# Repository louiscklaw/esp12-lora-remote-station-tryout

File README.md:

# esp12-lora-remote-station-tryout

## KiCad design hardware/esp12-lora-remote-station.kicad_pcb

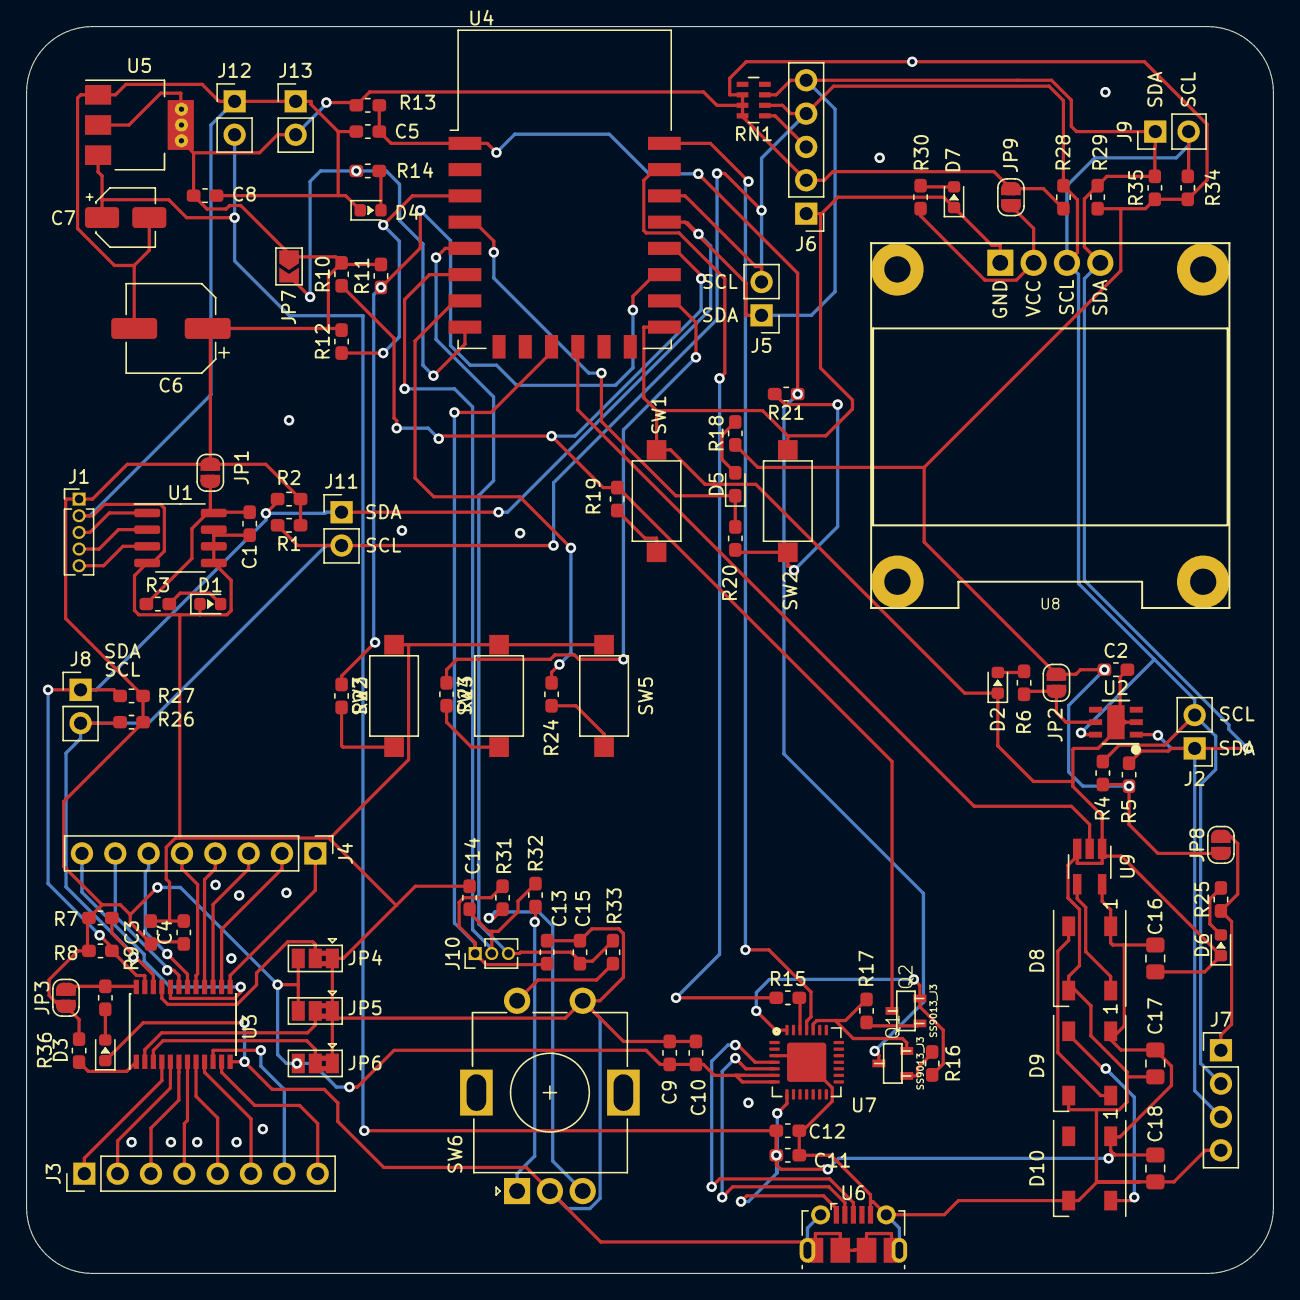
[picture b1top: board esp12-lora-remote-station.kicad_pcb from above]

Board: 2 copper layers, 95.0 x 95.0 mm, 104 parts (0 on the bottom side), 73 nets.

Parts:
C1: C103,0603; C_0603_1608Metric_Pad1.05x0.95mm_HandSolder
C2, C3, C8, C9, C11: C106,0603; C_0603_1608Metric_Pad1.05x0.95mm_HandSolder
C4, C5, C10, C12, C13, C14, C15: C104,0603; C_0603_1608Metric_Pad1.05x0.95mm_HandSolder
C6: CP100uf,10V; CP_Elec_6.3x5.3
C7: CP10uf,16V; CP_Elec_4x5.3
C16, C17, C18: C106,0805; C_0805_2012Metric_Pad1.15x1.40mm_HandSolder
D1, D2, D3, D4, D6, D7: LED_GREEN,0603; LED_0603_1608Metric
D5: LED_BLUE,0603; LED_0603_1608Metric_Pad1.05x0.95mm_HandSolder
D8, D9, D10: WS2812B; LED_WS2812B_5050_white
J1: LM75_HEADER; PinHeader_1x05_P1.27mm_Vertical
J2, J5, J8, J9, J11: I2C_HEADER,2.54; I2C_DEBUG,2.54
J3: P0_HEADER; PinHeader_1x08_P2.54mm_Vertical
J4: P1_HEADER; PinHeader_1x08_P2.54mm_Vertical
J6: I2C_HEADER; PinHeader_1x05_P2.54mm_Vertical
J7: GSM_TX_HEADER; PinHeader_1x04_P2.54mm_Vertical
J10: ROT_ENC_HEADER; PinHeader_1x03_P1.27mm_Vertical
J12, J13: 5V_header; PinHeader_1x02_P2.54mm_Vertical
JP1: LM75_EN; SolderJumper-2_P1.3mm_Open_RoundedPad1.0x1.5mm
JP2: SHT20_EN; SolderJumper-2_P1.3mm_Open_RoundedPad1.0x1.5mm
JP3: PCF8575C_EN; SolderJumper-2_P1.3mm_Open_RoundedPad1.0x1.5mm
JP4: A0; SolderJumper-3_P1.3mm_Bridged2Bar12_Pad1.0x1.5mm
JP5: A1; SolderJumper-3_P1.3mm_Bridged2Bar12_Pad1.0x1.5mm
JP6: A2; SolderJumper-3_P1.3mm_Bridged2Bar12_Pad1.0x1.5mm
JP7: SolderJumper_2_Open_arrow; SolderJumper-2_P1.3mm_Open_TrianglePad1.0x1.5mm
JP8: PWR_EN; SolderJumper-2_P1.3mm_Open_RoundedPad1.0x1.5mm
JP9: SolderJumper_2_Open_round; SolderJumper-2_P1.3mm_Open_RoundedPad1.0x1.5mm
Q1, Q2: SS9013_J3; 9013,J3,SOT23
R1, R2, R4, R5, R7, R8, R26, R27, R28, R29, R34, R35: R473,0603; R_0603_1608Metric_Pad1.05x0.95mm_HandSolder
R3, R6, R9, R14, R25, R30: R511,0603; R_0603_1608Metric_Pad1.05x0.95mm_HandSolder
R10, R11, R12, R13, R16, R17: R123,0603; R_0603_1608Metric_Pad1.05x0.95mm_HandSolder
R15, R18, R19, R21, R22, R23, R24: R471,0603; R_0603_1608Metric_Pad1.05x0.95mm_HandSolder
R20: R0,0603; R_0603_1608Metric_Pad1.05x0.95mm_HandSolder
R31, R32, R33: R273,0603; R_0603_1608Metric_Pad1.05x0.95mm_HandSolder
R36: R104,0603; R_0603_1608Metric_Pad1.05x0.95mm_HandSolder
RN1: RN_472,0603; R_Array_Concave_4x0603
SW1: FLASH_BUTTON; SW_SPST_CK_RS282G05A3
SW2: SW_RESET,2_leg,SMD; SW_SPST_CK_RS282G05A3
SW3, SW5: USER_BUTTON1; SW_SPST_CK_RS282G05A3
SW4: USER_BUTTON2; SW_SPST_CK_RS282G05A3
SW6: EC11_VERTICAL; RotaryEncoder_Alps_EC11E_Vertical_H20mm
U1: LM75; SOP-8_3.76x4.96mm_P1.27mm
U2: SHT20
U3: PCF8575C
U4: ESP12; ESP-12E
U5: AMS1117-3.3; AMS1117_SOT-223
U6: USB_Micro; USB_Micro-B_Molex-105017-0001
U7: CP2102; CP2102_qfn28
U8: SSD1306-OLED-I2C; OLED_096_12864_SSD1306
U9: 74AHCT1G125; SOT-23-5_HandSoldering

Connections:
+3V3: C2.1, C3.1, C4.1, C6.1, C8.1, C9.1, C10.1, J1.1, J6.2, J13.2, JP1.1, JP2.1, JP3.1, JP4.3, JP5.3, JP6.3, JP7.1, JP8.1, JP9.1, R1.1, R2.1, R4.1, R5.1, R7.1, R8.1, R10.2, R11.2, R12.2, R13.2, R18.1, R26.1, R27.1, R28.1, R29.1, R34.1, R35.1, R36.1, RN1.6, RN1.7, RN1.8, U5.2, U7.6, U7.7
+5V: C7.1, C11.1, C12.1, C16.2, C17.2, C18.2, D8.1, D9.1, D10.1, J12.2, U5.3, U6.1, U7.8, U9.5
/SCL: J2.SCL, J5.SCL, J6.4, J7.2, J8.SCL, J9.SCL, J11.SCL, R1.2, R4.2, R7.2, R26.2, R28.2, R34.2, RN1.2, U2.6, U3.22, U4.20, U8.SCL
/SDA: J2.SDA, J5.SDA, J6.5, J7.3, J8.SDA, J9.SDA, J11.SDA, R2.2, R5.2, R8.2, R27.2, R29.2, R35.2, RN1.3, U2.1, U3.23, U4.19, U8.SDA
/WS2812/WS2812_IN: U4.12, U9.2
/digital_input/A0: JP4.2, U3.21
/digital_input/A1: JP5.2, U3.2
/digital_input/A2: JP6.2, U3.3
/digital_input/INT: R36.2, U3.1
/digital_input/P10: J4.1, U3.13
/digital_input/P11: J4.2, U3.14
/digital_input/P12: J4.3, U3.15
/digital_input/P13: J4.4, U3.16
/digital_input/P14: J4.5, U3.17
/digital_input/P15: J4.6, U3.18
/digital_input/P16: J4.7, U3.19
/digital_input/P17: J4.8, U3.20
/digital_input/PO0: J3.1, U3.4
/digital_input/PO1: J3.2, U3.5
/digital_input/PO2: J3.3, U3.6
/digital_input/PO3: J3.4, U3.7
/digital_input/PO4: J3.5, U3.8
/digital_input/PO5: J3.6, U3.9
/digital_input/PO6: J3.7, U3.10
/digital_input/PO7: J3.8, U3.11
/esp12_core/EN: R12.1, U4.3
/esp12_core/GPIO0: Q2.3, R10.1, R19.1, U4.18
/esp12_core/GPIO2: R11.1, R22.1, U4.17
/esp12_core/GPIO13: R24.1, U4.7
/esp12_core/GPIO14: C15.1, J10.3, R33.2, U4.5
/esp12_core/GPIO15: R23.1, U4.16
/esp12_core/GPIO16: D5.1, R20.1, U4.4
/esp12_core/INT: J6.3, RN1.1
/esp12_core/RXD0: R15.1, U4.21
/esp12_core/TXD0: U4.22, U7.25
/esp12_core/nRST: C5.1, Q1.3, R13.1, R21.1, U4.1
/esp12_core/usb_to_uart/DTR: Q2.2, R16.1, U7.28
/esp12_core/usb_to_uart/D_N: U6.2, U7.5
/esp12_core/usb_to_uart/D_P: U6.3, U7.4
/esp12_core/usb_to_uart/RTS: Q1.2, R17.1, U7.24
/user_button/A: C13.1, J10.1, R31.2, U4.11
/user_button/B: C14.1, J10.2, R32.2, U4.6
GND: C1.2, C2.2, C3.2, C4.2, C5.2, C6.2, C7.2, C8.2, C9.2, C10.2, C11.2, C12.2, C13.2, C14.2, C15.2, C16.1, C17.1, C18.1, D1.1, D2.1, D3.1, D4.1, D6.1, D7.1, D8.3, D9.3, D10.3, J1.2, J6.1, J7.4, J12.1, J13.1, JP4.1, JP5.1, JP6.1, SW1.2, SW2.2, SW3.2, SW4.2, SW5.2, SW6.C, SW6.E, U1.4, U1.5, U1.6, U1.7, U2.2, U2.PAD, U3.12, U4.15, U5.1, U6.5, U6.6, U6.7, U6.8, U6.9, U7.3, U7.29, U8.GND, U9.1, U9.3
unnamed: C1.1, JP1.2, R3.1, U1.8
unnamed: D1.2, R3.2
unnamed: D2.2, R6.2
unnamed: D3.2, R9.2
unnamed: D4.2, R14.2
unnamed: D5.2, R18.2
unnamed: D6.2, R25.2
unnamed: D7.2, R30.2
unnamed: D8.2, D9.4
unnamed: D8.4, U9.4
unnamed: D9.2, D10.4
unnamed: J1.3, U1.1
unnamed: J1.4, U1.2
unnamed: J1.5, U1.3
unnamed: J7.1, JP8.2, R25.1
unnamed: JP2.2, R6.1, U2.5
unnamed: JP3.2, R9.1, U3.24
unnamed: JP7.2, R14.1, U4.8
unnamed: JP9.2, R30.1, U8.VCC
unnamed: Q1.1, R16.2
unnamed: Q2.1, R17.2
unnamed: R15.2, U7.26
unnamed: R19.2, SW1.1
unnamed: R20.2, R21.2, SW2.1
unnamed: R22.2, SW3.1
unnamed: R23.2, SW4.1
unnamed: R24.2, SW5.1
unnamed: R31.1, SW6.B
unnamed: R32.1, SW6.A
unnamed: R33.1, SW6.D

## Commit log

2019-06-01 init commit,
2019-06-01 after DRC,
2019-06-01 after routing,
2019-06-01 update manual rout,
2019-06-01 update DRC ok,
2019-06-01 update copper pour,
2019-06-01 send to fab,
2019-06-13 update for datasheet,
2019-06-19 update,
2019-06-20 update for RESET BUTTON,
2020-05-05 ci: init travis token,
2020-05-05 ci: init travis build config,
